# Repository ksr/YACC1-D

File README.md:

# YACC1-D — the definitive YACC1 tree

**Status (2026-09-28):** the single source of truth for YACC1, on GitHub at `github.com/ksr/YACC1-D`, migrated from
the old `YACCS/` folders on 2026-09-19/20. What is in the machine today: `docs/system/MACHINE.md`; which board
revisions exist and were made: `hardware/FABRICATED.md`; what is open: `BACKLOG.md`.

**Who made it:** YACC1 is my project: I designed and built the hardware and wrote the original microcode, monitor,
Tiny BASIC and emulator. Claude, Anthropic's AI, has been directly involved in the design, coding and documentation
since 2026; the header at the top of every source file says who wrote it. — Ken Rother

**Working on it:** `CLAUDE.md` (the working notes for Claude sessions) has the standing rules, the machine facts that
bite, where things are and how to build and test. On a new Mac: clone, `python3 tools/setup_check.py` (which tools are
missing, and the command for each), `make` (the C tools), then `make check`.

## What YACC1 is

YACC1 ("Yet Another Custom CPU") is a hand-built 8-bit TTL computer: an 8-bit accumulator and TMP register, eight
16-bit registers R0-R7, microcoded, on a 96-pin bus. The cards: backplane, a two-board sequencer (logic + microcode
memory), ALU, two index-register cards, memory (RAM, the 8K ROM, TMP registers), I/O (16550 UART console, switches,
LEDs, TIL311s), a 6845 video card in bring-up, and a bus tester for driving the bus by hand.

Around the hardware, all in this tree:

- **Firmware in the machine:** the microcode (a C generator that writes the sequencer's EEPROM image), the monitor
  ROM with its Intel-hex loader, BIOS vectors and video driver, and a Tiny BASIC.
- **Y1/OS:** a disk operating system on CompactFlash (P8XFS), with a shell, redirection and pipes, and some thirty-five
  `/bin` commands, most ported from P8X, among them `vi`, `sed`, `awk`, `pack` and `kermit`. It exists twice and is kept
  in step: `os/y1os.asm` (the real one) and `os/y1os.c` (its specification).
- **y1cc**, a C compiler for YACC1: a Python reference, a C twin, and nine passes that run under Y1/OS. Together with
  the on-target assembler `/bin/asm` they rebuild themselves byte for byte on the emulator (the self-host).
- **Host tools:** the RC/asm assembler, an instruction-level emulator, a microcode-level emulator that steps the real
  EEPROM image through models of the cards, loaders for the ROM monitor and the sequencer card, Kermit, the CF-card
  writer, and the KiCad board tooling.

Before this tree the work was spread over nine overlapping copies under `YACCS/` (Eagle variants, four git clones with
different histories, backups). YACC1-D keeps the *current* version of every board, program, tool, test and document in
one place, with everything superseded kept but frozen. `MIGRATION.md` and `migration/` record where every file came
from.

## The tree

```
YACC1-D/
├── README.md  CLAUDE.md  BACKLOG.md  MIGRATION.md
├── Makefile                  make (the C tools), make check (everything, ~11 min), os-test, cc-test, native-test, ...
├── docs/
│   ├── system/               MACHINE.md (what is built), architecture, memory map, microcode, OS plan
│   ├── isa/                  a timing diagram per instruction, the microcode review
│   ├── cards/                theory of operation, one per card
│   ├── programming/          assembler, monitor, OS, C compiler, emulators, memory map, I/O ports
│   ├── procedures/           bring-up, CF card, testing, Kermit
│   ├── bom/                  bills of material, one per card
│   ├── history/              dated design notes kept verbatim (2016-2021), presentations
│   ├── datasheets/           third-party PDFs the designs use
│   └── references/           external papers and books
├── hardware/
│   ├── bus/                  backplane, bus template, bus jumpers, blank card
│   ├── cards/<card>/         one folder per card (below)
│   ├── libraries/            eagle/: the Eagle .lbr/.dru files the designs use
│   ├── mechanical/           card divider clips, switch template, spacers
│   ├── FABRICATED.md         every revision of every board: built, in the machine, or design only
│   ├── SCHEMATICS.md BOARDS.md   generated indexes of the schematic and board PDFs
│   ├── KICAD.md              the Eagle -> KiCad conversion and its netlist proof
│   └── reviews/              the indexes of the multi-card design reviews (2026-09-21: mechanical, datapath,
│                             control and I/O); the reviews themselves are in each board's own reviews/
├── firmware/                 code that runs INSIDE the machine
│   ├── microcode/            ucode-generator2 (C) -> test.hex, the sequencer EEPROM image
│   ├── monitor/  basic/      monitor.asm, basic.asm (+ candidates never burned)
│   ├── rom/                  shipped/ (the image to burn and what is burned), builds/, captured chips
│   └── abi/                  BIOS vectors, variable and port map (still to be written)
├── os/                       Y1/OS: y1os.asm + y1os.c, commands/ (C), commands-asm/ (asm.asm, basic.asm), lib_*.c,
│                             man/, docs/, Makefile -> os/disk.img
├── software/                 host-side toolchain (runs on the Mac)
│   ├── assembler/            RC/asm + yacc1.def
│   ├── emulator/             instruction-level emulator (the ISA reference)
│   ├── ucemu/                microcode-level emulator (test.hex through models of the cards, CF, video)
│   ├── y1dbg/                the debugger for ucemu (y1ucemu -D + a curses UI with the live video screen)
│   ├── gatemodel/            cards at gate level from their netlists (the video card for y1ucemu -G)
│   ├── compiler/             y1cc.py, c/ (y1cc.c and the passes cc1..cc9), lib/
│   ├── disassembler/         disasm2
│   └── ubasic-c/             the C uBASIC the assembly BASIC was ported from
├── embedded/                 Arduino sketches for the support cards, built against libraries/ only
│   ├── sequencer-card/       sequencer4 (the microcode loader in the machine), dumpram, deprecated/
│   ├── bus-tester/           bus-driver, bus-monitor, bus-test, led-switch-test
│   ├── clocker/              external single-step clock
│   ├── command-sender/       Processing host for bus-tester scripts (to be replaced by Python)
│   └── libraries/            vendored: YACC_Common_header.h (bus table), Adafruit_MCP23017 1.1.0
├── tools/                    host scripts: setup_check, verify_firmware/embedded, ucode_send, monload, cfcard,
│                             y1kermit, p8xfs, the KiCad/Eagle tooling, the tree audit
├── tests/                    os, compiler, native (self-host), asm, disasm, bench (the machine), monload, kermit,
│                             cfcard, video, sequencer, ucemu, y1dbg, memory, assembler, bus-tester-scripts
├── mk/                       shared make fragments
├── migration/                the 2026-09-19/20 migration's inventory, plan and logs
├── vm/                       manifests of VMs and legacy installers (the images live outside git)
├── media/                    photos of the boards
├── website/                  the project website: MkDocs over these docs (website/README.md), live at yacc1.cottageworker.com
└── archive/                  frozen, never edited: gen1-2015-2018 (the first YACC1), superseded-revisions,
                              eagle-projects, third-party, conflict-losers (older duplicates from the migration)
```

## Card folder layout (`hardware/cards/<card>/`)

```
<card>/
├── README.md        what the card is, current revision, what is built, open issues
├── kicad/<rev>/     KiCad 10 projects, GENERATED from the Eagle files by tools/eagle_to_kicad_all.py with a
│                    schematic-vs-board netlist proof (hardware/KICAD.md) - except where a MASTER marker says the
│                    KiCad project is hand-maintained and IS the design (memory v2.0, CF v1.0, video v1.1);
│                    those have a build.sh (route with Freerouting, DRC, gerbers, renders, BOM)
├── eagle/<rev>/     the Eagle originals, frozen; the active revision at the top, fab/ (what was sent to the board
│                    house), pdf/ (generated), bom/
│   └── deprecated/  every older revision, same shape
├── reviews/         the card's design reviews, one file per review (<rev>-<review>-<date>.md, or <rev>.md)
└── docs/            card-specific notes
```

| Card | In the machine | Designed, not built |
|---|---|---|
| backplane | V2.0 (8 slots) | |
| sequencer-logic | v2.1 | v2.2 "CPU off" switch (idea, BACKLOG) |
| sequencer-memory | V2.1 + EEPROM adaptor | |
| alu | V3.2 | |
| register (index registers) | 1.1, two cards (R0-R3, R4-R7) | |
| io | V1.1 | |
| memory | v1.3 | **v2.0**: v1.3 + the CompactFlash interface on P8/P9, finished for fabrication |
| video | V1.0, no 6845 fitted yet | **v1.1** (KiCad master), changes still to make before ordering |
| cf | | v1.0, a separate CF card, superseded by memory v2.0 |
| bus-tester | V1.1 (2016; a bench tool) | V3.1 (2020, never ordered) |
| mem-switch, mem-register | bring-up cards (switch ROM at $0000, 16-byte RAM at $0010), fitted when needed | |
| protocard, address-tmp | built (address-tmp retired) | |

Bus items live under `hardware/bus/`: backplane, bus-template V3.2, bus jumpers (built, obsolete, not fitted), blank
card V3.1 (built) and V3.2 (the template for new cards).

## Conventions

- One authoritative copy of anything. Duplicates were the whole problem.
- Lower-case, hyphenated directory names; no spaces (the Eagle tree's spaces broke scripts repeatedly).
- Binary images (ROM, microcode hex) are committed **with** their source and a script that rebuilds them and
  diffs against the committed file; `make check` does it for all of them.
- Every file is explained: `tools/audit_tree.py` must report 0 unexplained after every commit.
- Files that came from YACCS are edited only with a dated entry in `tools/patched_files.txt`.
- Third-party code and libraries are vendored under a folder that says so, with their licence.
- Anything under `archive/` or `deprecated/` is never edited.
- Every `.rtf` note has a generated Markdown twin beside it (`tools/rtf_to_md.py`).
- No git LFS. Very large binaries (the 142 MB presentation, installers, VM images) live outside git, listed in `vm/`.

## How the migration was settled

- Repo: `~/Developer/YACC1-D` on both Macs (out of iCloud Drive, which corrupts `.git`), on GitHub, no LFS.
- History: started fresh (the first commit is the migration); the old `ksr/YACC1-2020` repo is not grafted in.
- `archive/` is committed (about 186 MB), and so are the datasheets.
- Older board revisions that were built stay with their card under `eagle/deprecated/`;
  `archive/superseded-revisions/` holds designs never built and the old tree's snapshots.
- Monitor and BASIC: the 2026 builds in `firmware/rom/shipped` are current; the 2021 `8afde21` build (ON/OFF, break-in)
  is kept as a candidate, never burned.
- Build environment: every C tool has a plain Makefile (2026-09-20); the NetBeans `nbproject/` folders are kept but
  no longer needed.

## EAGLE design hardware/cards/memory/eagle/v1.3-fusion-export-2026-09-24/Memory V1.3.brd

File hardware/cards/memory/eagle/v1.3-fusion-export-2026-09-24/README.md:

# Memory card v1.3 — the BUILT card (Fusion 360 export, 2026-09-24)

This folder is the record of the memory card that is in the machine: the design JLCPCB fabricated on 2025-06-27
(order 2000765A, 4-layer FR-4). Ken exported it from Fusion 360 on 2026-09-24 in Eagle format. The older
`../v1.3/` folder is an **earlier save** of the same revision (notes 2025-03-06, board file 2021-03-17) and is
**not** the built card. See "How it differs from the earlier save" below.

| File | What it is | Original name |
|---|---|---|
| `Memory V1.3.sch` | schematic, Eagle 9.7.0 XML (Fusion export) | `Memory_V1.3.sch` |
| `Memory V1.3.brd` | board, Eagle 9.7.0 XML (Fusion export): 177.8 x 114.0 mm, 4 layers (1 Top, 2 = GND plane, 15 = VCC plane, 16 Bottom), 53 parts, 1,263 tracks, 114 vias | `Memory V1.3.brd` |
| `fab/jlcpcb-order-2000765A-Y42.zip` | JLCPCB's order archive, downloaded as it came. `YG/PCB_2000765A_Y42.zip` inside is the gerber set JLCPCB received (Fusion CAM job "Memory V1.3 v4", 2025-06-27: 15 files, gerbers + drill + part list + pick-and-place); `YG/4te.json` has the order parameters (4 layers, FR-4); `ok/` holds JLCPCB's processed CAM data | `Memory V1_2025-06-27_Y42.zip` |
| `pdf/` | schematic and per-layer board PDFs (generated by `tools/sch_to_pdf.py` / `tools/brd_to_pdf.py`) | - |
| `FABRICATED` | marker (generated by `tools/gen_fabricated.py` from `tools/fabricated.py`) | - |

The KiCad conversion (proven, schematic vs board) is `../../kicad/v1.3-fusion-export-2026-09-24/`.

## Proof that this is what was fabricated

`tools/verify_fab_vs_brd.py` compares the board file with the order's gerber set without using KiCad (it parses
the Eagle XML, the Excellon drill file and the RS-274X copper layers itself). Re-run it from the repository root:

```
python3 tools/verify_fab_vs_brd.py "hardware/cards/memory/eagle/v1.3-fusion-export-2026-09-24/Memory V1.3.brd" \
    hardware/cards/memory/eagle/v1.3-fusion-export-2026-09-24/fab/jlcpcb-order-2000765A-Y42.zip \
    --same-as "hardware/cards/memory/eagle/v1.3/fab/Memory V1_2025-06-27.zip"
```

Result (2026-09-24): **PASS**

- Holes: the board has 695 (579 pads, 114 vias, 2 mounting holes); the drill file has 695. Every one matches in
  position (0.01 mm) and diameter; nothing extra on either side. Sizes: 0.254 mm x 114 (vias), 0.813 x 456,
  1.016 x 123, 2.794 x 2.
- Tracks: all 576 Top and all 687 Bottom wires (all 0.1524 mm = 6 mil) are strokes of the same width in
  `copper_top_l1.gbr` / `copper_bottom_l4.gbr`. The gerbers' remaining strokes (407 per side) all lie inside pads:
  that is how Eagle draws the oval DIP pads. No other stroke.
- Planes: the board's only inner-layer copper is one polygon per layer, layer 2 = GND and layer 15 = VCC; the
  inner gerbers are filled regions.
- Parts: the fab part list names the same 53 parts as the board, including IC15 (74ALS11N) and IC26-IC29
  (74LS374N); the pick-and-place puts all 53 at the board's coordinates.
- The gerber set in the order archive is byte-identical, all 15 files, to `../v1.3/fab/Memory V1_2025-06-27.zip`
  (which the tree already had; that zip belongs to this design, not to the earlier save beside it).

Control: the same check against the earlier save (`../v1.3/Memory V1.3.brd`) FAILS (178 of its holes are not in
the drill file, 226 drill hits are not on that board, hundreds of tracks differ; the part list has IC15, the board
does not).

## How it differs from the earlier save in `../v1.3/`

Schematic (the only circuit change): **IC15, a 74ALS11 triple 3-input AND**. Gate A (pins 1, 2, 13 -> 12) =
AND(-LO-RAM, -HI-RAM, -ROM-CS) drives net N$21 -> IC5 pin 19, the enable (-G) of the 74LS245 data-bus buffer. In
the earlier save IC5 pin 19 sits on -VMA. With IC15 the buffer is enabled only while one of the card's own chips
(low RAM, high RAM or ROM) is selected, so it no longer drives the data bus for a block the card leaves undecoded:
v1.3 added the IC7 jumper block so any 4K block can be taken out of the map for memory-mapped I/O, and the video
card answers in the $D000 block; with -VMA as the enable the memory card's buffer would fight the video card on
every read there. Gates B and C have their inputs grounded. The jumper-block nets are also named in the export
(SEL0-7 = IC7 outputs, RAM0-7, ROM0-7 = the jumper returns; they were N$5..N$44), same connectivity.

Board: IC15 is placed (151.13, 53.34) and routed; the TMP registers IC26-IC29 (74LS374, 154.94 / 105.41-67.16)
and the resistor networks RN5/RN6 are on the board and routed (in the earlier save they sat off the board with
their connections unrouted: its KiCad conversion lists 100 unconnected items). All of this board's copper is in
the order's gerbers (above).

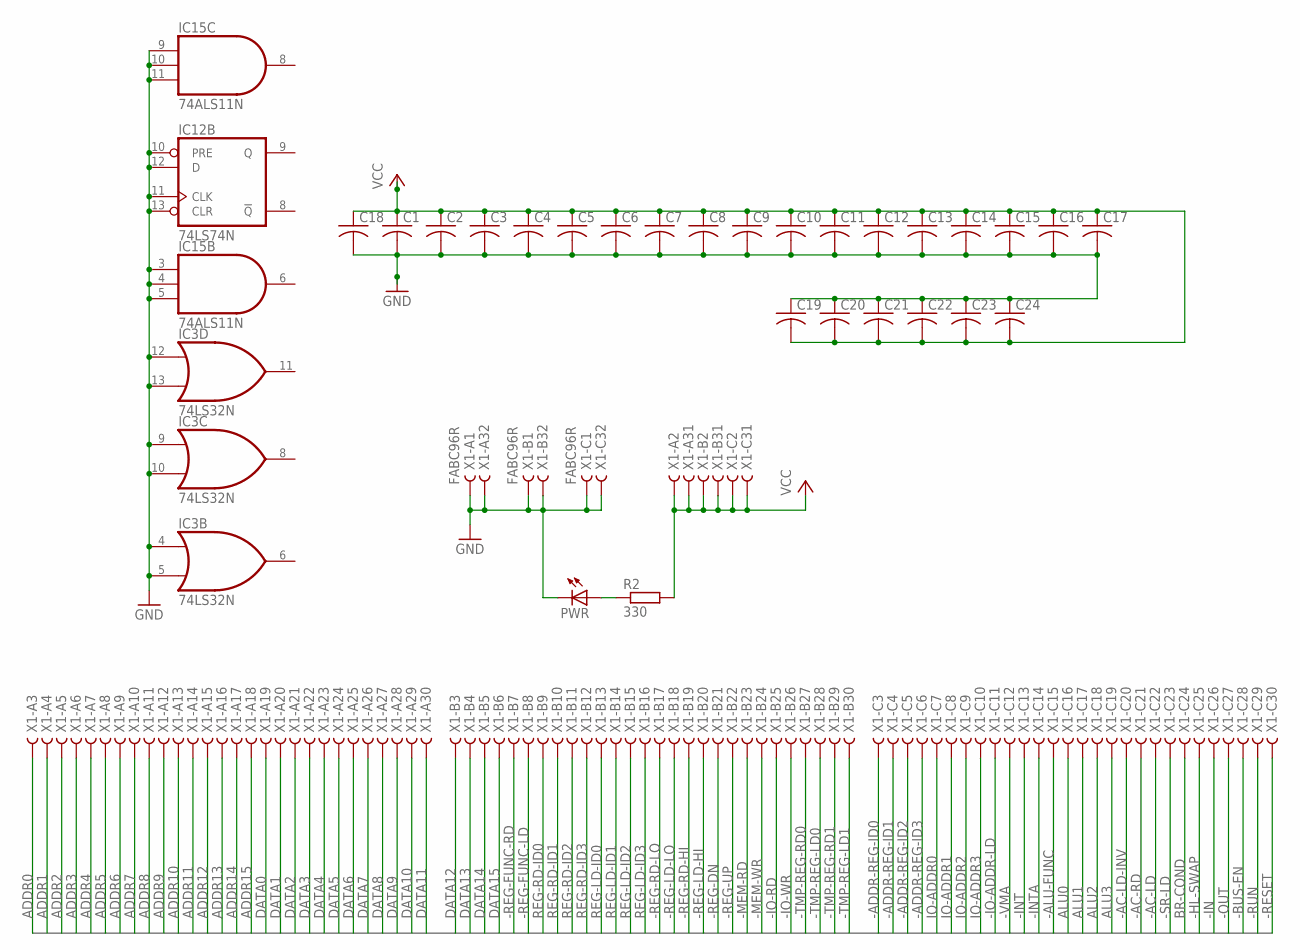
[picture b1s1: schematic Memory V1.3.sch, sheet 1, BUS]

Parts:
C1, C2, C3, C4, C5, C6, C7, C8, C9, C10, C11, C12, C13, C14, C15, C16, C17, C18, C19, C20, C21, C22, C23, C24: C-US025-025X050; C025-025X050
IC3: 74LS32N; DIL14
IC12: 74LS74N; DIL14
IC15: 74ALS11N; DIL14
PWR: LED5MM
R2: 330; 0207/10
X1: FABC96R

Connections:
-AC-LD: X1.C22
-AC-LD-INV: X1.C20
-AC-RD: X1.C21
-ADDR-REG-ID0: X1.C3
-ADDR-REG-ID1: X1.C4
-ADDR-REG-ID2: X1.C5
-ADDR-REG-ID3: X1.C6
-ALU-FUNC: X1.C15
-BUS-EN: X1.C28; also elsewhere on the board
-HL-SWAP: X1.C25
-IN: X1.C26
-INT: X1.C13
-INTA: X1.C14
-IO-ADDR-LD: X1.C11
-IO-RD: X1.B25
-IO-WR: X1.B26
-MEM-RD: X1.B23; also elsewhere on the board
-MEM-WR: X1.B24; also elsewhere on the board
-OUT: X1.C27
-REG-DN: X1.B21
-REG-FUNC-LD: X1.B8
-REG-FUNC-RD: X1.B7
-REG-LD-HI: X1.B20
-REG-LD-LO: X1.B18
-REG-RD-HI: X1.B19
-REG-RD-LO: X1.B17
-REG-UP: X1.B22
-RESET: X1.C30; also elsewhere on the board
-RUN: X1.C29
-SR-LD: X1.C23
-TMP-REG-LD0: X1.B28; also elsewhere on the board
-TMP-REG-LD1: X1.B30; also elsewhere on the board
-TMP-REG-RD0: X1.B27; also elsewhere on the board
-TMP-REG-RD1: X1.B29; also elsewhere on the board
-VMA: X1.C12; also elsewhere on the board
ADDR0: X1.A3; also elsewhere on the board
ADDR1: X1.A4; also elsewhere on the board
ADDR2: X1.A5; also elsewhere on the board
ADDR3: X1.A6; also elsewhere on the board
ADDR4: X1.A7; also elsewhere on the board
ADDR5: X1.A8; also elsewhere on the board
ADDR6: X1.A9; also elsewhere on the board
ADDR7: X1.A10; also elsewhere on the board
ADDR8: X1.A11; also elsewhere on the board
ADDR9: X1.A12; also elsewhere on the board
ADDR10: X1.A13; also elsewhere on the board
ADDR11: X1.A14; also elsewhere on the board
ADDR12: X1.A15; also elsewhere on the board
ADDR13: X1.A16; also elsewhere on the board
ADDR14: X1.A17; also elsewhere on the board
ADDR15: X1.A18; also elsewhere on the board
ALU0: X1.C16
ALU1: X1.C17
ALU2: X1.C18
ALU3: X1.C19
BR-COND: X1.C24
DATA0: X1.A19; also elsewhere on the board
DATA1: X1.A20; also elsewhere on the board
DATA2: X1.A21; also elsewhere on the board
DATA3: X1.A22; also elsewhere on the board
DATA4: X1.A23; also elsewhere on the board
DATA5: X1.A24; also elsewhere on the board
DATA6: X1.A25; also elsewhere on the board
DATA7: X1.A26; also elsewhere on the board
DATA8: X1.A27; also elsewhere on the board
DATA9: X1.A28; also elsewhere on the board
DATA10: X1.A29; also elsewhere on the board
DATA11: X1.A30; also elsewhere on the board
DATA12: X1.B3; also elsewhere on the board
DATA13: X1.B4; also elsewhere on the board
DATA14: X1.B5; also elsewhere on the board
DATA15: X1.B6; also elsewhere on the board
GND: C1.2, C2.2, C3.2, C4.2, C5.2, C6.2, C7.2, C8.2, C9.2, C10.2, C11.2, C12.2, C13.2, C14.2, C15.2, C16.2, C17.2, C18.2, C19.1, C20.1, C21.1, C22.1, C23.1, C24.1, IC3.4 (I0), IC3.5 (I1), IC3.7 (GND), IC3.9 (I0), IC3.10 (I1), IC3.12 (I0), IC3.13 (I1), IC12.7 (GND), IC12.10 (PRE), IC12.11 (CLK), IC12.12 (D), IC12.13 (CLR), IC15.3 (I0), IC15.4 (I1), IC15.5 (I2), IC15.7 (GND), IC15.9 (I0), IC15.10 (I1), IC15.11 (I2), PWR.K (C), X1.A1, X1.A32, X1.B1, X1.B32, X1.C1, X1.C32; also elsewhere on the board
IO-ADDR0: X1.C7
IO-ADDR1: X1.C8
IO-ADDR2: X1.C9
IO-ADDR3: X1.C10
unnamed: PWR.A, R2.1
REG-LD-ID0: X1.B13
REG-LD-ID1: X1.B14
REG-LD-ID2: X1.B15
REG-LD-ID3: X1.B16
REG-RD-ID0: X1.B9
REG-RD-ID1: X1.B10
REG-RD-ID2: X1.B11
REG-RD-ID3: X1.B12
VCC: C1.1, C2.1, C3.1, C4.1, C5.1, C6.1, C7.1, C8.1, C9.1, C10.1, C11.1, C12.1, C13.1, C14.1, C15.1, C16.1, C17.1, C18.1, C19.2, C20.2, C21.2, C22.2, C23.2, C24.2, IC3.14 (VCC), IC12.14 (VCC), IC15.14 (VCC), R2.2, X1.A2, X1.A31, X1.B2, X1.B31, X1.C2, X1.C31; also elsewhere on the board

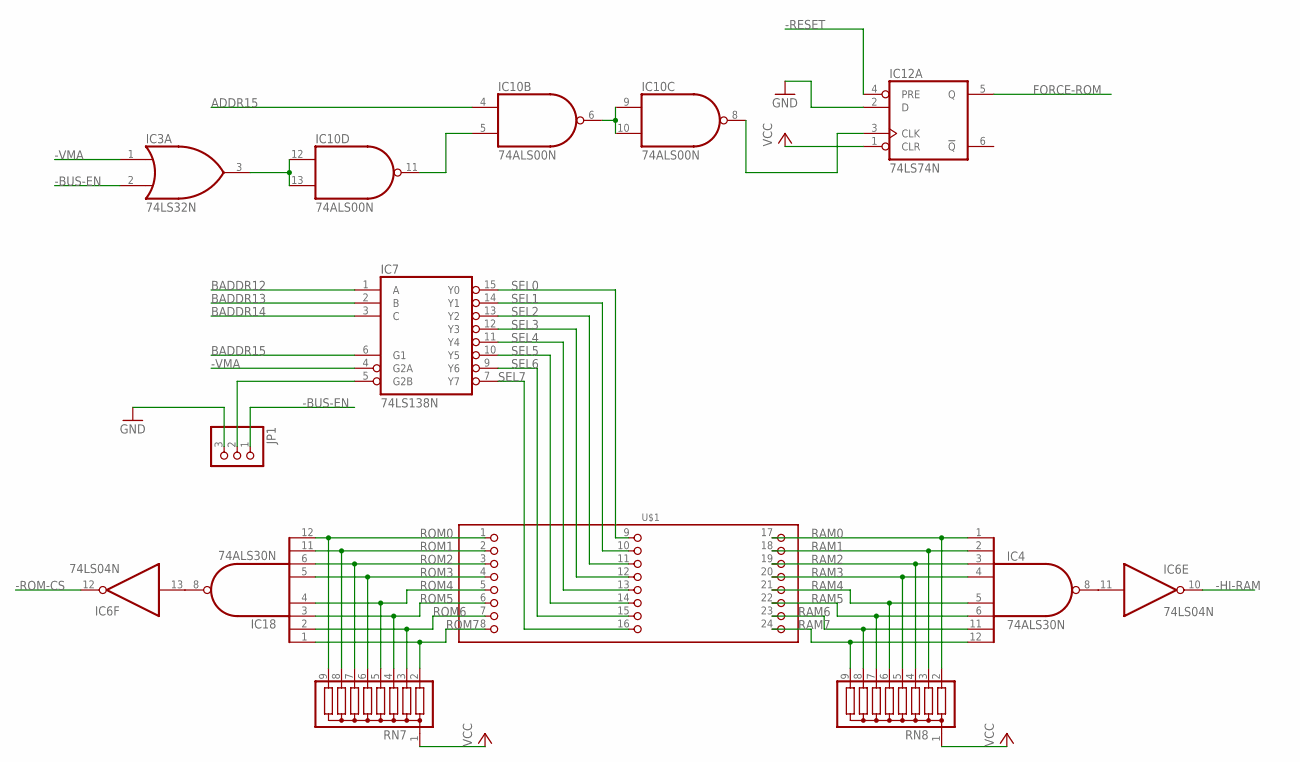
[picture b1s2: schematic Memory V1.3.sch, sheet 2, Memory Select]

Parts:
IC3: 74LS32N; DIL14
IC4, IC18: 74ALS30N; DIL14
IC6: 74LS04N; DIL14
IC7: 74LS138N; DIL16
IC10: 74ALS00N; DIL14
IC12: 74LS74N; DIL14
JP1: PINHD-1X3; 1X03
RN7, RN8: G08R; SIL9
U$1: PIN_3X8

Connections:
-BUS-EN: IC3.2 (I1), JP1.1; also elsewhere on the board
-HI-RAM: IC6.10 (O); also elsewhere on the board
-RESET: IC12.4 (PRE); also elsewhere on the board
-ROM-CS: IC6.12 (O); also elsewhere on the board
-VMA: IC3.1 (I0), IC7.4 (G2A); also elsewhere on the board
ADDR15: IC10.4 (I0); also elsewhere on the board
BADDR12: IC7.1 (A); also elsewhere on the board
BADDR13: IC7.2 (B); also elsewhere on the board
BADDR14: IC7.3 (C); also elsewhere on the board
BADDR15: IC7.6 (G1); also elsewhere on the board
FORCE-ROM: IC12.5 (Q); also elsewhere on the board
GND: IC3.7 (GND), IC4.7 (GND), IC6.7 (GND), IC7.8 (GND), IC10.7 (GND), IC12.2 (D), IC12.7 (GND), IC18.7 (GND), JP1.3; also elsewhere on the board
unnamed: IC6.13 (I), IC18.8 (O)
unnamed: IC4.8 (O), IC6.11 (I)
unnamed: IC10.8 (O), IC12.3 (CLK)
unnamed: IC10.6 (O), IC10.9 (I0), IC10.10 (I1)
unnamed: IC10.5 (I1), IC10.11 (O)
unnamed: IC7.5 (G2B), JP1.2
unnamed: IC3.3 (O), IC10.12 (I0), IC10.13 (I1)
RAM0: IC4.1 (I0), RN8.2, U$1.17
RAM1: IC4.2 (I1), RN8.3, U$1.18
RAM2: IC4.3 (I2), RN8.4, U$1.19
RAM3: IC4.4 (I3), RN8.5, U$1.20
RAM4: IC4.5 (I4), RN8.6, U$1.21
RAM5: IC4.6 (I5), RN8.7, U$1.22
RAM6: IC4.11 (I6), RN8.8, U$1.23
RAM7: IC4.12 (I7), RN8.9, U$1.24
ROM0: IC18.12 (I7), RN7.9, U$1.1
ROM1: IC18.11 (I6), RN7.8, U$1.2
ROM2: IC18.6 (I5), RN7.7, U$1.3
ROM3: IC18.5 (I4), RN7.6, U$1.4
ROM4: IC18.4 (I3), RN7.5, U$1.5
ROM5: IC18.3 (I2), RN7.4, U$1.6
ROM6: IC18.2 (I1), RN7.3, U$1.7
ROM7: IC18.1 (I0), RN7.2, U$1.8
SEL0: IC7.15 (Y0), U$1.9
SEL1: IC7.14 (Y1), U$1.10
SEL2: IC7.13 (Y2), U$1.11
SEL3: IC7.12 (Y3), U$1.12
SEL4: IC7.11 (Y4), U$1.13
SEL5: IC7.10 (Y5), U$1.14
SEL6: IC7.9 (Y6), U$1.15
SEL7: IC7.7 (Y7), U$1.16
VCC: IC3.14 (VCC), IC4.14 (VCC), IC6.14 (VCC), IC7.16 (VCC), IC10.14 (VCC), IC12.1 (CLR), IC12.14 (VCC), IC18.14 (VCC), RN7.1, RN8.1; also elsewhere on the board

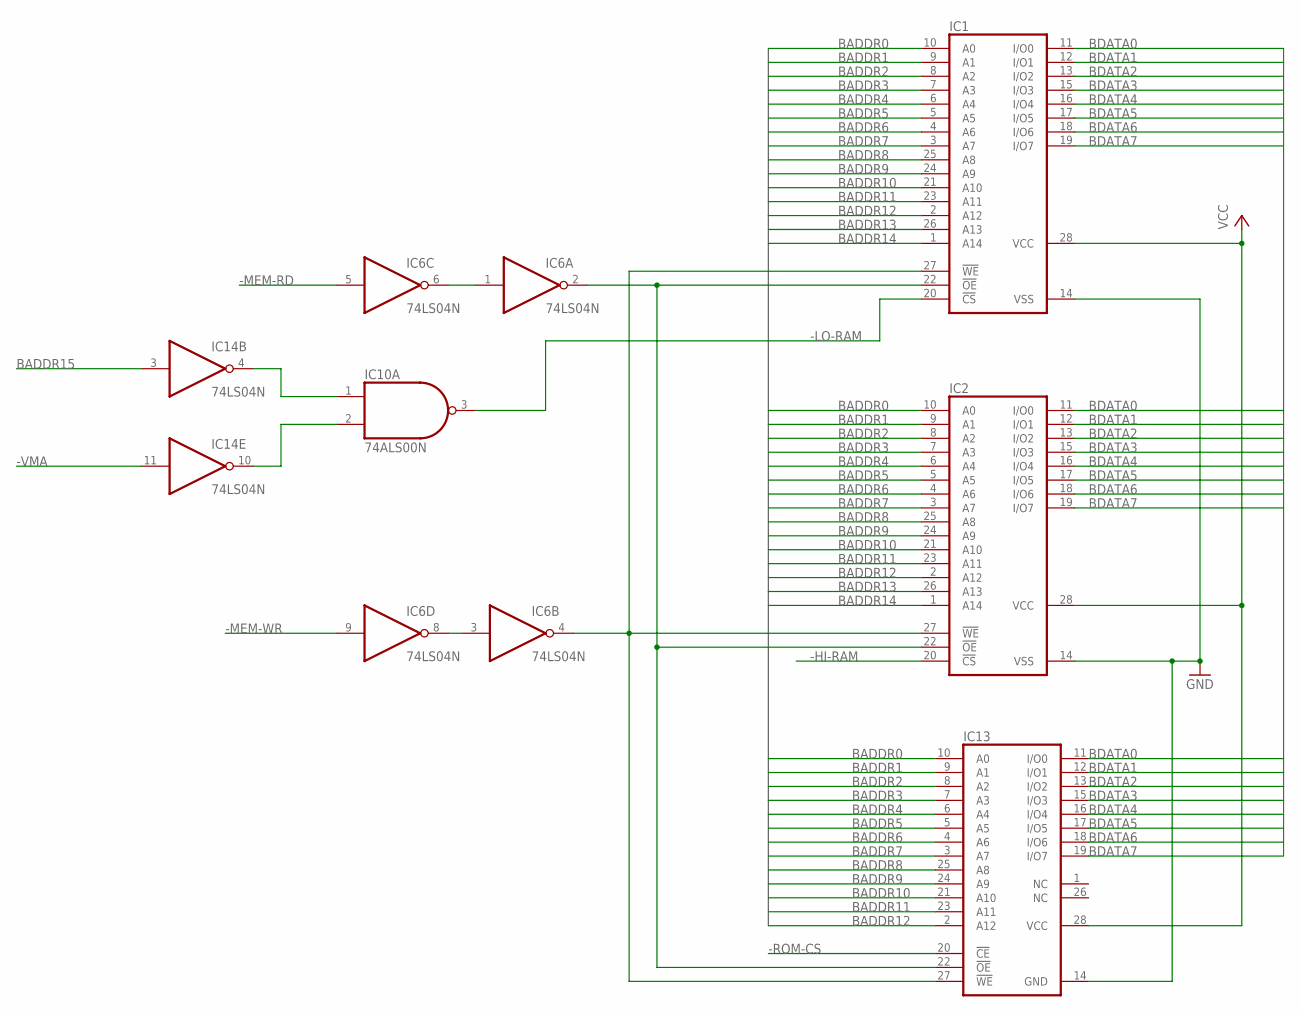
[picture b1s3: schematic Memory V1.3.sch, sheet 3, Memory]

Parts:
IC1, IC2: 62256P; DIL28-6
IC6, IC14: 74LS04N; DIL14
IC10: 74ALS00N; DIL14
IC13: 28C64C; DIL28-6

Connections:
-HI-RAM: IC2.20 (!CS); also elsewhere on the board
-LO-RAM: IC1.20 (!CS), IC10.3 (O); also elsewhere on the board
-MEM-RD: IC6.5 (I); also elsewhere on the board
-MEM-WR: IC6.9 (I); also elsewhere on the board
-ROM-CS: IC13.20 (!CE); also elsewhere on the board
-VMA: IC14.11 (I); also elsewhere on the board
BADDR0: IC1.10 (A0), IC2.10 (A0), IC13.10 (A0); also elsewhere on the board
BADDR1: IC1.9 (A1), IC2.9 (A1), IC13.9 (A1); also elsewhere on the board
BADDR2: IC1.8 (A2), IC2.8 (A2), IC13.8 (A2); also elsewhere on the board
BADDR3: IC1.7 (A3), IC2.7 (A3), IC13.7 (A3); also elsewhere on the board
BADDR4: IC1.6 (A4), IC2.6 (A4), IC13.6 (A4); also elsewhere on the board
BADDR5: IC1.5 (A5), IC2.5 (A5), IC13.5 (A5); also elsewhere on the board
BADDR6: IC1.4 (A6), IC2.4 (A6), IC13.4 (A6); also elsewhere on the board
BADDR7: IC1.3 (A7), IC2.3 (A7), IC13.3 (A7); also elsewhere on the board
BADDR8: IC1.25 (A8), IC2.25 (A8), IC13.25 (A8); also elsewhere on the board
BADDR9: IC1.24 (A9), IC2.24 (A9), IC13.24 (A9); also elsewhere on the board
BADDR10: IC1.21 (A10), IC2.21 (A10), IC13.21 (A10); also elsewhere on the board
BADDR11: IC1.23 (A11), IC2.23 (A11), IC13.23 (A11); also elsewhere on the board
BADDR12: IC1.2 (A12), IC2.2 (A12), IC13.2 (A12); also elsewhere on the board
BADDR13: IC1.26 (A13), IC2.26 (A13); also elsewhere on the board
BADDR14: IC1.1 (A14), IC2.1 (A14); also elsewhere on the board
BADDR15: IC14.3 (I); also elsewhere on the board
BDATA0: IC1.11 (I/O0), IC2.11 (I/O0), IC13.11 (I/O0); also elsewhere on the board
BDATA1: IC1.12 (I/O1), IC2.12 (I/O1), IC13.12 (I/O1); also elsewhere on the board
BDATA2: IC1.13 (I/O2), IC2.13 (I/O2), IC13.13 (I/O2); also elsewhere on the board
BDATA3: IC1.15 (I/O3), IC2.15 (I/O3), IC13.15 (I/O3); also elsewhere on the board
BDATA4: IC1.16 (I/O4), IC2.16 (I/O4), IC13.16 (I/O4); also elsewhere on the board
BDATA5: IC1.17 (I/O5), IC2.17 (I/O5), IC13.17 (I/O5); also elsewhere on the board
BDATA6: IC1.18 (I/O6), IC2.18 (I/O6), IC13.18 (I/O6); also elsewhere on the board
BDATA7: IC1.19 (I/O7), IC2.19 (I/O7), IC13.19 (I/O7); also elsewhere on the board
GND: IC1.14 (VSS), IC2.14 (VSS), IC6.7 (GND), IC10.7 (GND), IC13.14 (GND), IC14.7 (GND); also elsewhere on the board
MEM-RD: IC6.1 (I), IC6.6 (O)
unnamed: IC6.3 (I), IC6.8 (O)
unnamed: IC1.22 (!OE), IC2.22 (!OE), IC6.2 (O), IC13.22 (!OE)
unnamed: IC1.27 (!WE), IC2.27 (!WE), IC6.4 (O), IC13.27 (!WE)
unnamed: IC10.2 (I1), IC14.10 (O)
unnamed: IC10.1 (I0), IC14.4 (O)
VCC: IC1.28 (VCC), IC2.28 (VCC), IC6.14 (VCC), IC10.14 (VCC), IC13.28 (VCC), IC14.14 (VCC); also elsewhere on the board

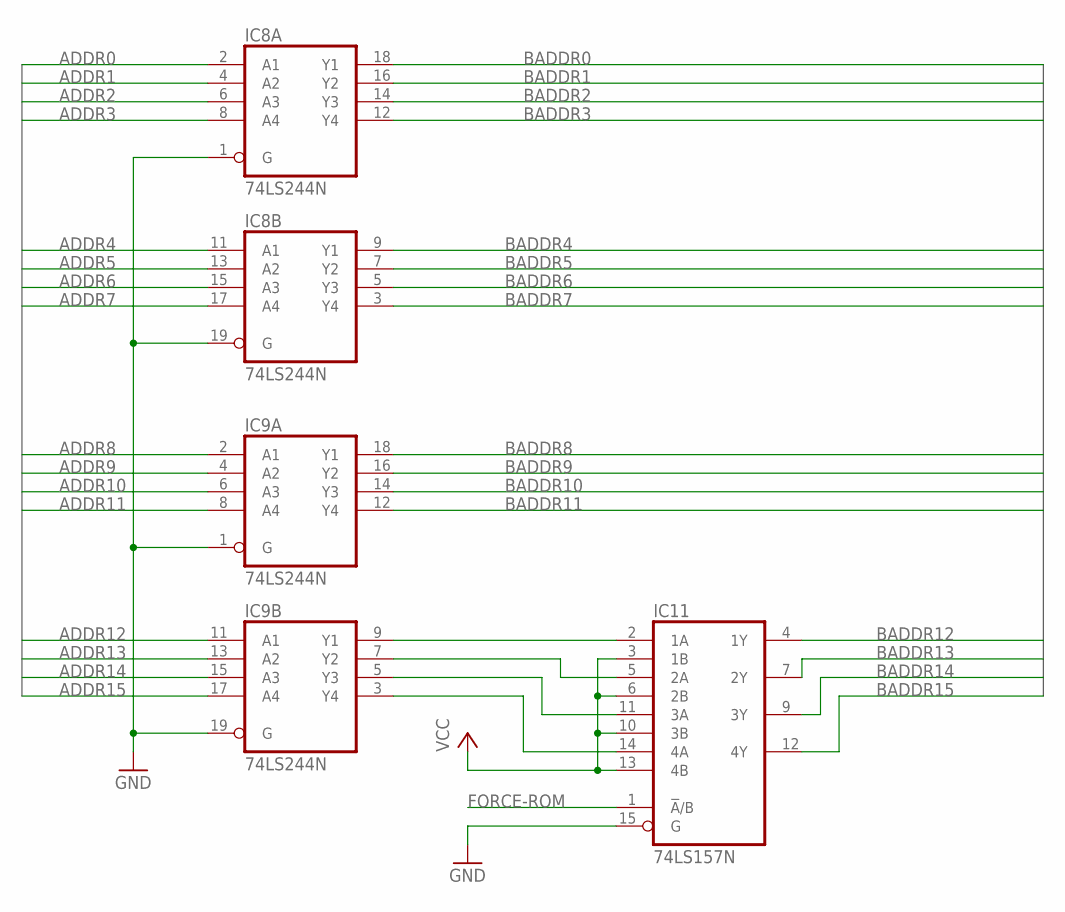
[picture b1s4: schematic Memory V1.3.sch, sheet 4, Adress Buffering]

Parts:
IC8, IC9: 74LS244N; DIL20
IC11: 74LS157N; DIL16

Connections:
ADDR0: IC8.2 (A1); also elsewhere on the board
ADDR1: IC8.4 (A2); also elsewhere on the board
ADDR2: IC8.6 (A3); also elsewhere on the board
ADDR3: IC8.8 (A4); also elsewhere on the board
ADDR4: IC8.11 (A1); also elsewhere on the board
ADDR5: IC8.13 (A2); also elsewhere on the board
ADDR6: IC8.15 (A3); also elsewhere on the board
ADDR7: IC8.17 (A4); also elsewhere on the board
ADDR8: IC9.2 (A1); also elsewhere on the board
ADDR9: IC9.4 (A2); also elsewhere on the board
ADDR10: IC9.6 (A3); also elsewhere on the board
ADDR11: IC9.8 (A4); also elsewhere on the board
ADDR12: IC9.11 (A1); also elsewhere on the board
ADDR13: IC9.13 (A2); also elsewhere on the board
ADDR14: IC9.15 (A3); also elsewhere on the board
ADDR15: IC9.17 (A4); also elsewhere on the board
BADDR0: IC8.18 (Y1); also elsewhere on the board
BADDR1: IC8.16 (Y2); also elsewhere on the board
BADDR2: IC8.14 (Y3); also elsewhere on the board
BADDR3: IC8.12 (Y4); also elsewhere on the board
BADDR4: IC8.9 (Y1); also elsewhere on the board
BADDR5: IC8.7 (Y2); also elsewhere on the board
BADDR6: IC8.5 (Y3); also elsewhere on the board
BADDR7: IC8.3 (Y4); also elsewhere on the board
BADDR8: IC9.18 (Y1); also elsewhere on the board
BADDR9: IC9.16 (Y2); also elsewhere on the board
BADDR10: IC9.14 (Y3); also elsewhere on the board
BADDR11: IC9.12 (Y4); also elsewhere on the board
BADDR12: IC11.4 (1Y); also elsewhere on the board
BADDR13: IC11.7 (2Y); also elsewhere on the board
BADDR14: IC11.9 (3Y); also elsewhere on the board
BADDR15: IC11.12 (4Y); also elsewhere on the board
FORCE-ROM: IC11.1 (!A!/B); also elsewhere on the board
GND: IC8.1 (G), IC8.10 (GND), IC8.19 (G), IC9.1 (G), IC9.10 (GND), IC9.19 (G), IC11.8 (GND), IC11.15 (G); also elsewhere on the board
unnamed: IC9.9 (Y1), IC11.2 (1A)
unnamed: IC9.7 (Y2), IC11.5 (2A)
unnamed: IC9.5 (Y3), IC11.11 (3A)
unnamed: IC9.3 (Y4), IC11.14 (4A)
VCC: IC8.20 (VCC), IC9.20 (VCC), IC11.3 (1B), IC11.6 (2B), IC11.10 (3B), IC11.13 (4B), IC11.16 (VCC); also elsewhere on the board

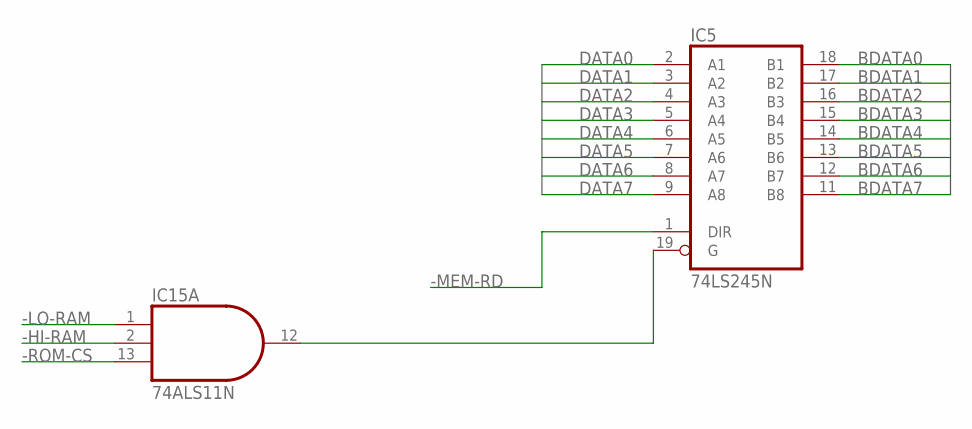
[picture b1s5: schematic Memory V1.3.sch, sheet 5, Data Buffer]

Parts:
IC5: 74LS245N; DIL20
IC15: 74ALS11N; DIL14

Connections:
-HI-RAM: IC15.2 (I1); also elsewhere on the board
-LO-RAM: IC15.1 (I0); also elsewhere on the board
-MEM-RD: IC5.1 (DIR); also elsewhere on the board
-ROM-CS: IC15.13 (I2); also elsewhere on the board
BDATA0: IC5.18 (B1); also elsewhere on the board
BDATA1: IC5.17 (B2); also elsewhere on the board
BDATA2: IC5.16 (B3); also elsewhere on the board
BDATA3: IC5.15 (B4); also elsewhere on the board
BDATA4: IC5.14 (B5); also elsewhere on the board
BDATA5: IC5.13 (B6); also elsewhere on the board
BDATA6: IC5.12 (B7); also elsewhere on the board
BDATA7: IC5.11 (B8); also elsewhere on the board
DATA0: IC5.2 (A1); also elsewhere on the board
DATA1: IC5.3 (A2); also elsewhere on the board
DATA2: IC5.4 (A3); also elsewhere on the board
DATA3: IC5.5 (A4); also elsewhere on the board
DATA4: IC5.6 (A5); also elsewhere on the board
DATA5: IC5.7 (A6); also elsewhere on the board
DATA6: IC5.8 (A7); also elsewhere on the board
DATA7: IC5.9 (A8); also elsewhere on the board
GND: IC5.10 (GND), IC15.7 (GND); also elsewhere on the board
unnamed: IC5.19 (G), IC15.12 (O)
VCC: IC5.20 (VCC), IC15.14 (VCC); also elsewhere on the board

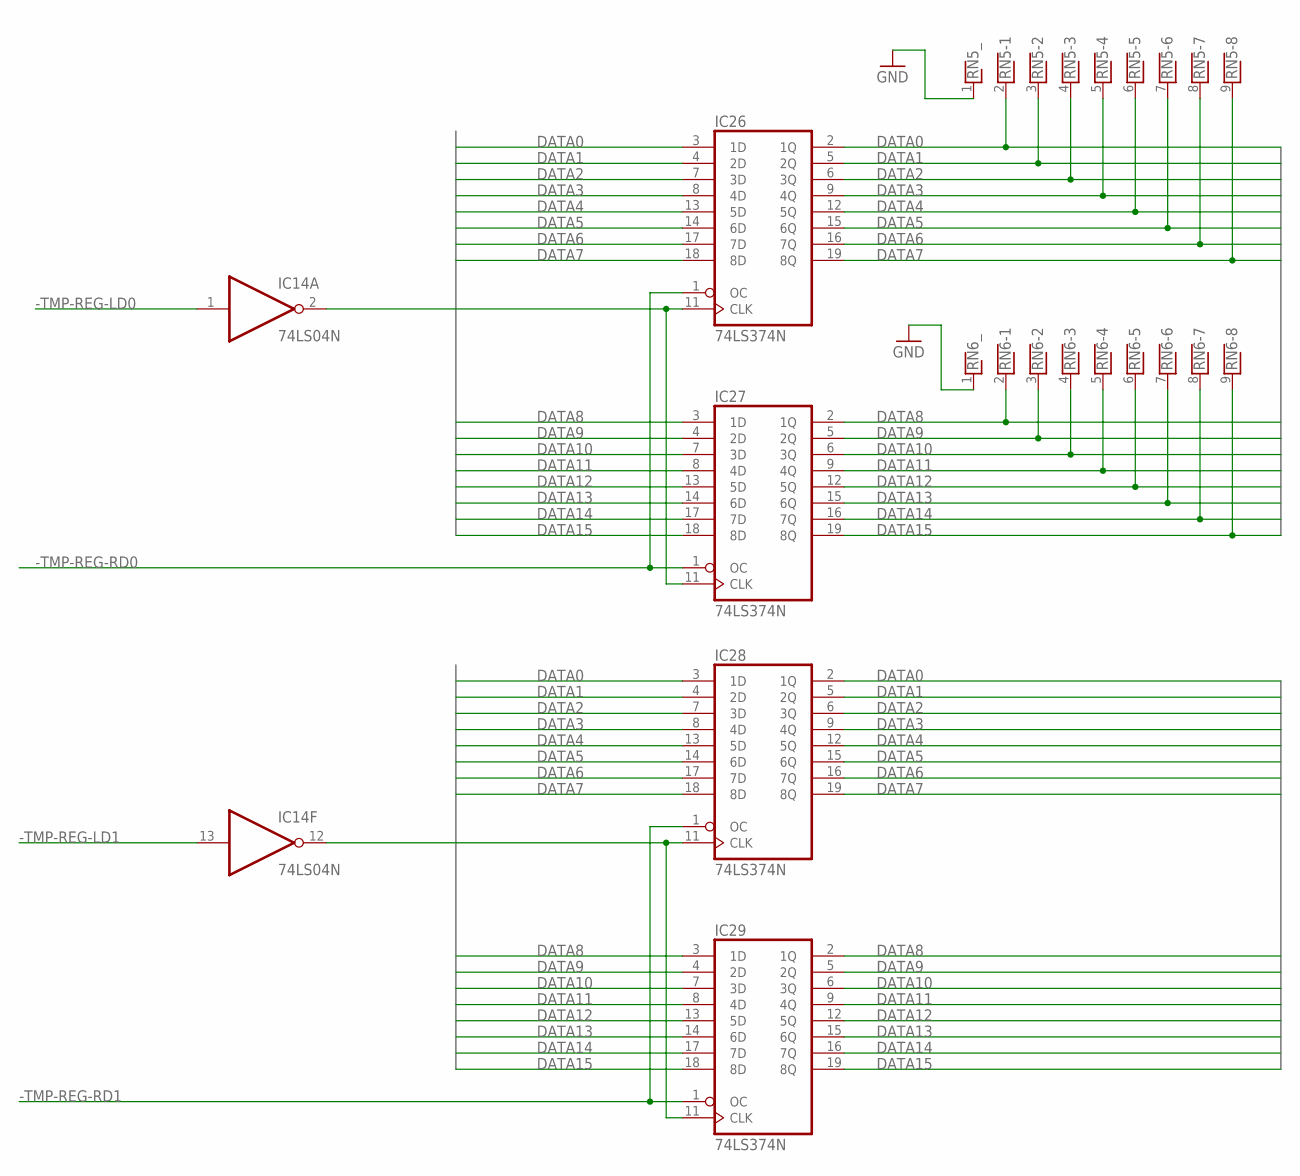
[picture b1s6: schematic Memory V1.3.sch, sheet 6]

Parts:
IC14: 74LS04N; DIL14
IC26, IC27, IC28, IC29: 74LS374N; DIL20
RN5, RN6: RNX8; RN-9

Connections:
-TMP-REG-LD0: IC14.1 (I); also elsewhere on the board
-TMP-REG-LD1: IC14.13 (I); also elsewhere on the board
-TMP-REG-RD0: IC26.1 (OC), IC27.1 (OC); also elsewhere on the board
-TMP-REG-RD1: IC28.1 (OC), IC29.1 (OC); also elsewhere on the board
DATA0: IC26.2 (1Q), IC26.3 (1D), IC28.2 (1Q), IC28.3 (1D), RN5.2; also elsewhere on the board
DATA1: IC26.4 (2D), IC26.5 (2Q), IC28.4 (2D), IC28.5 (2Q), RN5.3; also elsewhere on the board
DATA2: IC26.6 (3Q), IC26.7 (3D), IC28.6 (3Q), IC28.7 (3D), RN5.4; also elsewhere on the board
DATA3: IC26.8 (4D), IC26.9 (4Q), IC28.8 (4D), IC28.9 (4Q), RN5.5; also elsewhere on the board
DATA4: IC26.12 (5Q), IC26.13 (5D), IC28.12 (5Q), IC28.13 (5D), RN5.6; also elsewhere on the board
DATA5: IC26.14 (6D), IC26.15 (6Q), IC28.14 (6D), IC28.15 (6Q), RN5.7; also elsewhere on the board
DATA6: IC26.16 (7Q), IC26.17 (7D), IC28.16 (7Q), IC28.17 (7D), RN5.8; also elsewhere on the board
DATA7: IC26.18 (8D), IC26.19 (8Q), IC28.18 (8D), IC28.19 (8Q), RN5.9; also elsewhere on the board
DATA8: IC27.2 (1Q), IC27.3 (1D), IC29.2 (1Q), IC29.3 (1D), RN6.2; also elsewhere on the board
DATA9: IC27.4 (2D), IC27.5 (2Q), IC29.4 (2D), IC29.5 (2Q), RN6.3; also elsewhere on the board
DATA10: IC27.6 (3Q), IC27.7 (3D), IC29.6 (3Q), IC29.7 (3D), RN6.4; also elsewhere on the board
DATA11: IC27.8 (4D), IC27.9 (4Q), IC29.8 (4D), IC29.9 (4Q), RN6.5; also elsewhere on the board
DATA12: IC27.12 (5Q), IC27.13 (5D), IC29.12 (5Q), IC29.13 (5D), RN6.6; also elsewhere on the board
DATA13: IC27.14 (6D), IC27.15 (6Q), IC29.14 (6D), IC29.15 (6Q), RN6.7; also elsewhere on the board
DATA14: IC27.16 (7Q), IC27.17 (7D), IC29.16 (7Q), IC29.17 (7D), RN6.8; also elsewhere on the board
DATA15: IC27.18 (8D), IC27.19 (8Q), IC29.18 (8D), IC29.19 (8Q), RN6.9; also elsewhere on the board
GND: IC14.7 (GND), IC26.10 (GND), IC27.10 (GND), IC28.10 (GND), IC29.10 (GND), RN5.1, RN6.1; also elsewhere on the board
unnamed: IC14.2 (O), IC26.11 (CLK), IC27.11 (CLK)
unnamed: IC14.12 (O), IC28.11 (CLK), IC29.11 (CLK)
VCC: IC14.14 (VCC), IC26.20 (VCC), IC27.20 (VCC), IC28.20 (VCC), IC29.20 (VCC); also elsewhere on the board

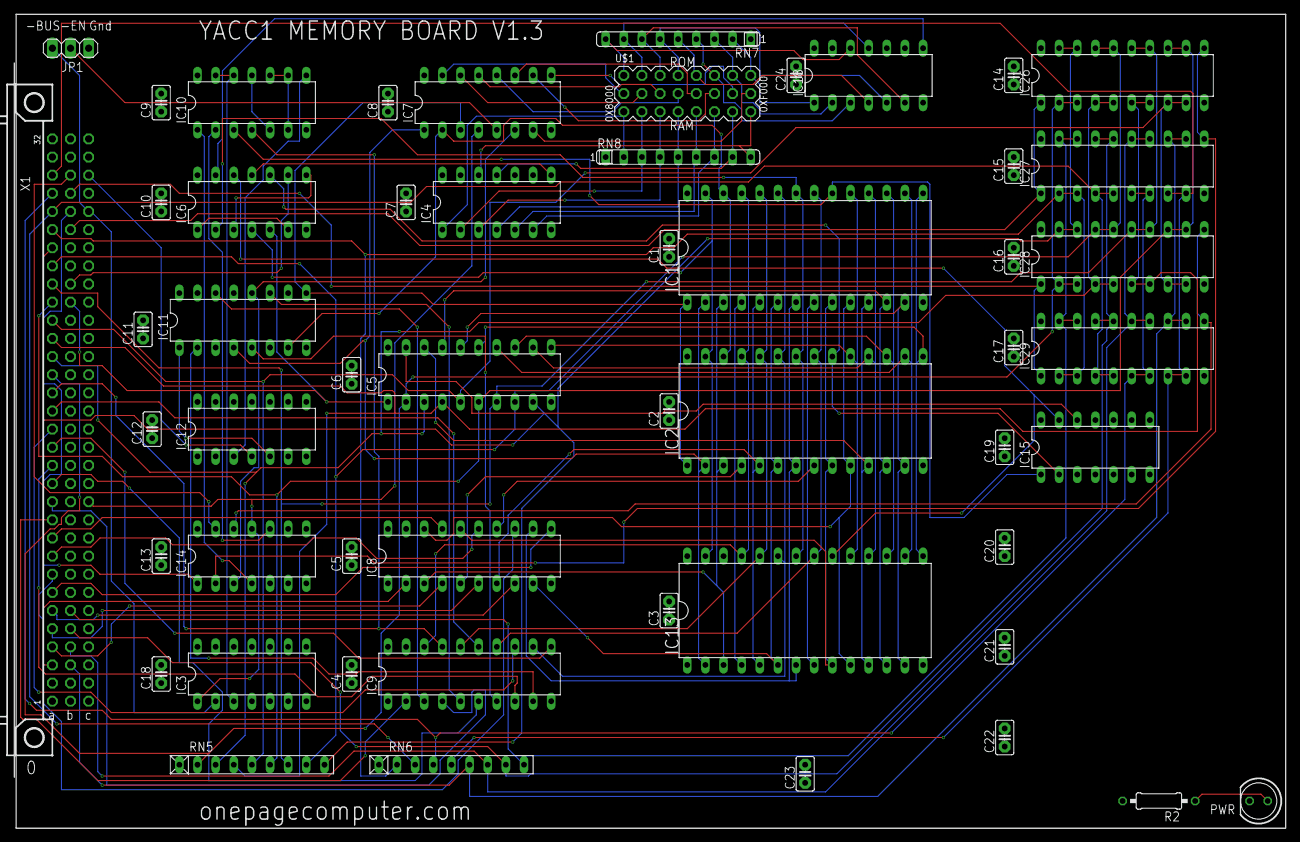
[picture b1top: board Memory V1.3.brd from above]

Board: 4 copper layers, 177.8 x 114.0 mm, 53 parts (0 on the bottom side), 116 nets.
